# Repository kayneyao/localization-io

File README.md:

# localization-io
An io board for the LSM6DSL 6 axis accel-gyro combo, LIS2MDL 3 axis mag, and ATGMH336H gps module for localization of systems using an RP2040 as the MCU

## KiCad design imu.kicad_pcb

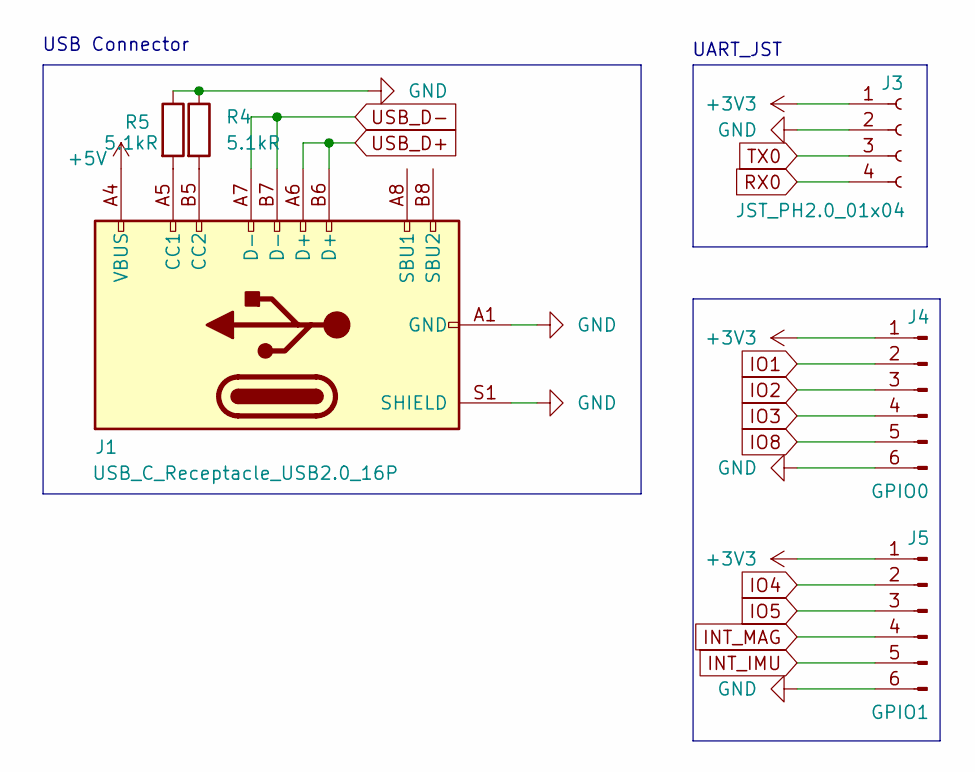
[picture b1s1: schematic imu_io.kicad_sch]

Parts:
J1: USB_C_Receptacle_USB2.0_16P; USB_C_Receptacle_GCT_USB4105-xx-A_16P_TopMnt_Horizontal
J3: JST_PH2.0_01x04; JST_PH_S4B-PH-K_1x04_P2.00mm_Horizontal
J4: GPIO0; PinHeader_1x06_P2.54mm_Vertical
J5: GPIO1; PinHeader_1x06_P2.54mm_Vertical
R4, R5: 5.1kR; R_0805_2012Metric_Pad1.20x1.40mm_HandSolder

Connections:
+3V3: J3.1, J4.1, J5.1; also elsewhere on the board
+5V: J1.A4 (VBUS), J1.A9 (VBUS), J1.B4 (VBUS), J1.B9 (VBUS); also elsewhere on the board
GND: J1.A1 (GND), J1.A12 (GND), J1.B1 (GND), J1.B12 (GND), J1.S1 (SHIELD), J3.2, J4.6, J5.6, R4.1, R5.1; also elsewhere on the board
INT_IMU: J5.5; also elsewhere on the board
INT_MAG: J5.4; also elsewhere on the board
IO1: J4.2; also elsewhere on the board
IO2: J4.3; also elsewhere on the board
IO3: J4.4; also elsewhere on the board
IO4: J5.2; also elsewhere on the board
IO5: J5.3; also elsewhere on the board
IO8: J4.5; also elsewhere on the board
unnamed: J1.A5 (CC1), R5.2
unnamed: J1.B5 (CC2), R4.2
RX0: J3.4; also elsewhere on the board
TX0: J3.3; also elsewhere on the board
USB_D+: J1.A6 (D+), J1.B6 (D+); also elsewhere on the board
USB_D-: J1.A7 (D-), J1.B7 (D-); also elsewhere on the board

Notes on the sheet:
USB Connector
UART_JST

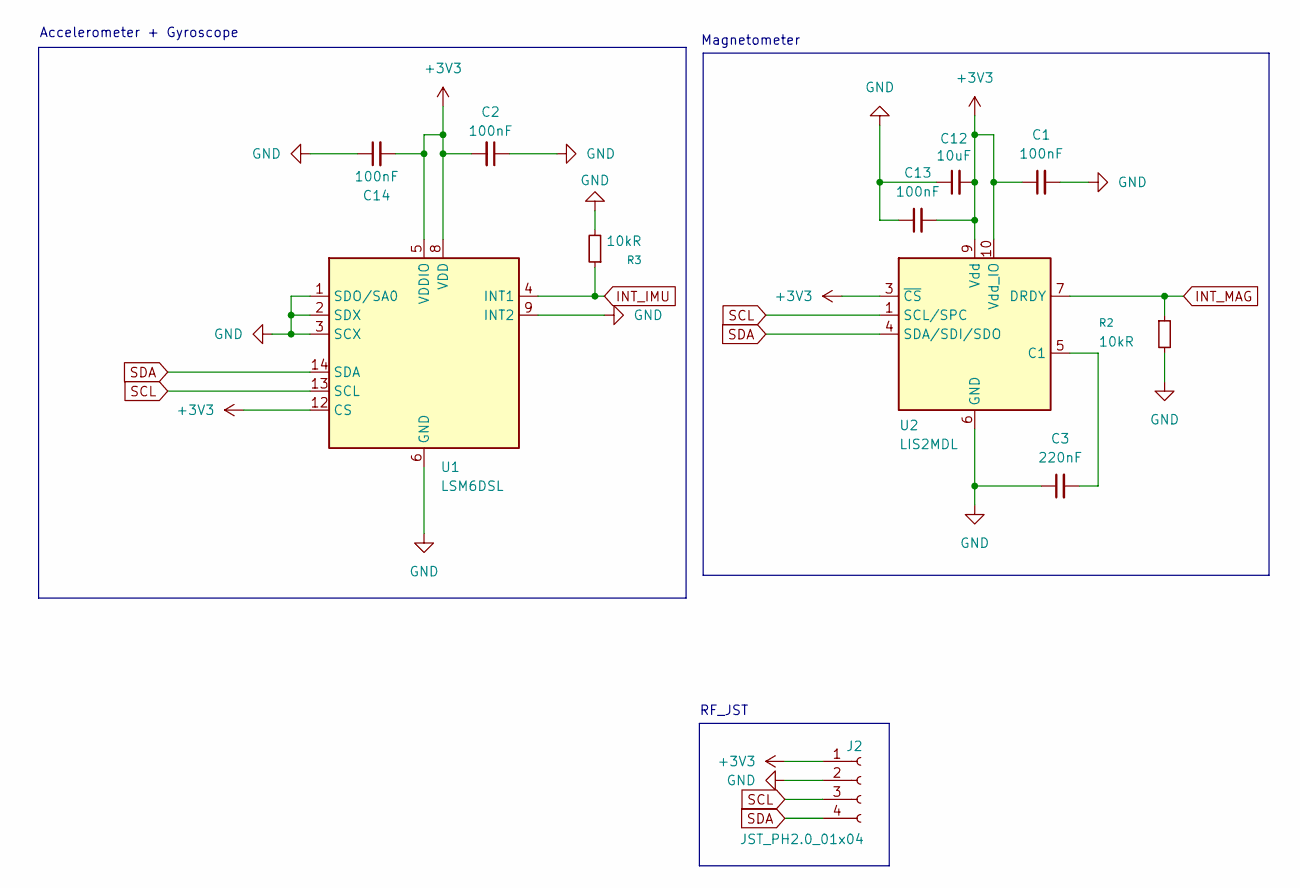
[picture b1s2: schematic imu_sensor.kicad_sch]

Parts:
C1, C2, C13, C14: 100nF; C_0805_2012Metric_Pad1.18x1.45mm_HandSolder
C3: 220nF; C_0805_2012Metric_Pad1.18x1.45mm_HandSolder
C12: 10uF; C_0805_2012Metric_Pad1.18x1.45mm_HandSolder
J2: JST_PH2.0_01x04; JST_PH_S4B-PH-K_1x04_P2.00mm_Horizontal
R2, R3: 10kR; R_0805_2012Metric_Pad1.20x1.40mm_HandSolder
U1: LSM6DSL; LGA-14_3x2.5mm_P0.5mm_LayoutBorder3x4y
U2: LIS2MDL; LGA-12_2x2mm_P0.5mm

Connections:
+3V3: C1.1, C2.2, C12.2, C13.2, C14.2, J2.1, U1.5 (VDDIO), U1.8 (VDD), U1.12 (CS), U2.3 (~CS), U2.9 (Vdd), U2.10 (Vdd_IO); also elsewhere on the board
GND: C1.2, C2.1, C3.1, C12.1, C13.1, C14.1, J2.2, R2.2, R3.2, U1.1 (SDO/SA0), U1.2 (SDX), U1.3 (SCX), U1.6 (GND), U1.7 (GND), U1.9 (INT2), U2.6 (GND), U2.8 (GND); also elsewhere on the board
INT_IMU: R3.1, U1.4 (INT1); also elsewhere on the board
INT_MAG: R2.1, U2.7 (DRDY); also elsewhere on the board
unnamed: C3.2, U2.5 (C1)
SCL: J2.3, U1.13 (SCL), U2.1 (SCL/SPC); also elsewhere on the board
SDA: J2.4, U1.14 (SDA), U2.4 (SDA/SDI/SDO); also elsewhere on the board

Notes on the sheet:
Accelerometer + Gyroscope
RF_JST
Magnetometer

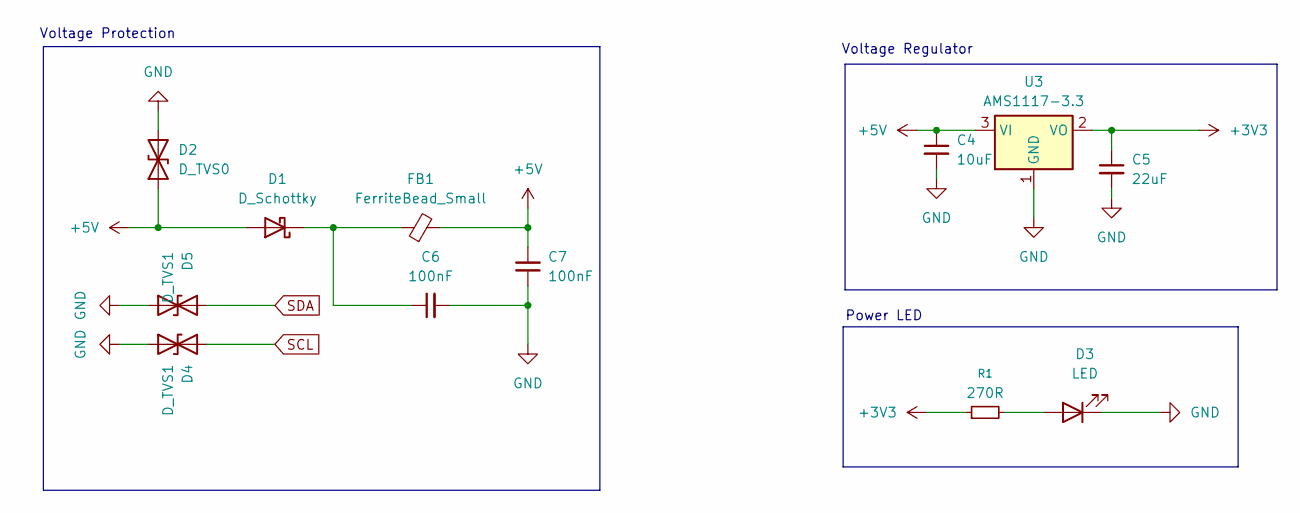
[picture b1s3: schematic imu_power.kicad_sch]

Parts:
C4: 10uF; C_0805_2012Metric_Pad1.18x1.45mm_HandSolder
C5: 22uF; C_0805_2012Metric_Pad1.18x1.45mm_HandSolder
C6, C7: 100nF; C_0805_2012Metric_Pad1.18x1.45mm_HandSolder
D1: D_Schottky; D_SOD-123F
D2: D_TVS0; D_SMB
D3: LED; LED_0805_2012Metric_Pad1.15x1.40mm_HandSolder
D4, D5: D_TVS1; D_SOD-323_HandSoldering
FB1: FerriteBead_Small; L_0805_2012Metric_Pad1.05x1.20mm_HandSolder
R1: 270R; R_0805_2012Metric_Pad1.20x1.40mm_HandSolder
U3: AMS1117-3.3; SOT-223-3_TabPin2

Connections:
+3V3: C5.1, R1.1, U3.2 (VO); also elsewhere on the board
+5V: C4.1, C7.2, D1.2 (A), D2.1 (A1), FB1.2, U3.3 (VI); also elsewhere on the board
GND: C4.2, C5.2, C6.2, C7.1, D2.2 (A2), D3.1 (K), D4.1 (A1), D5.1 (A1), U3.1 (GND); also elsewhere on the board
unnamed: C6.1, D1.1 (K), FB1.1
unnamed: D3.2 (A), R1.2
SCL: D4.2 (A2); also elsewhere on the board
SDA: D5.2 (A2); also elsewhere on the board

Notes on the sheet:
Voltage Protection
Power LED
Voltage Regulator

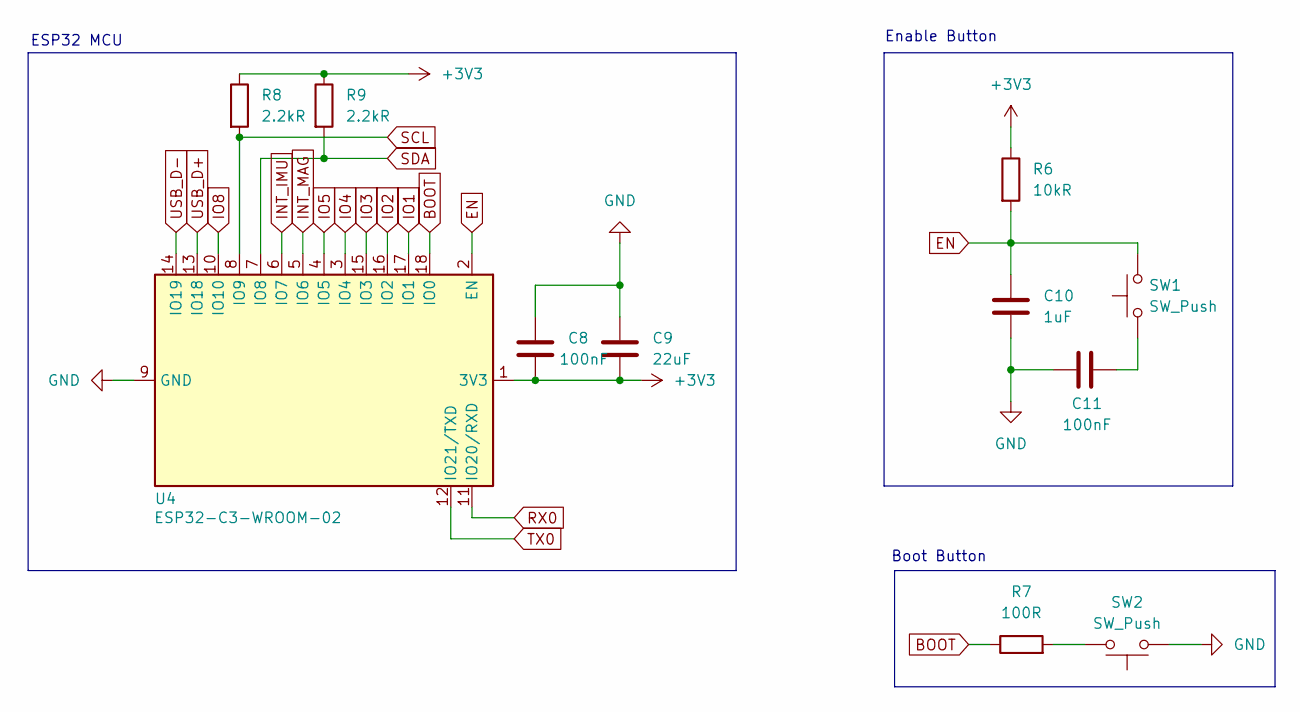
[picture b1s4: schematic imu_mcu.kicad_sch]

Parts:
C8, C11: 100nF; C_0805_2012Metric_Pad1.18x1.45mm_HandSolder
C9: 22uF; C_0805_2012Metric_Pad1.18x1.45mm_HandSolder
C10: 1uF; C_0805_2012Metric_Pad1.18x1.45mm_HandSolder
R6: 10kR; R_0805_2012Metric_Pad1.20x1.40mm_HandSolder
R7: 100R; R_0805_2012Metric_Pad1.20x1.40mm_HandSolder
R8, R9: 2.2kR; R_0805_2012Metric_Pad1.20x1.40mm_HandSolder
SW1, SW2: SW_Push; SW_Tactile_SPST_NO_Straight_CK_PTS636Sx25SMTRLFS
U4: ESP32-C3-WROOM-02

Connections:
+3V3: C8.2, C9.2, R6.1, R8.1, R9.1, U4.1 (3V3); also elsewhere on the board
BOOT: R7.1, U4.18 (IO0)
EN: C10.1, R6.2, SW1.2, U4.2 (EN)
GND: C8.1, C9.1, C10.2, C11.1, SW2.1, U4.9 (GND), U4.19 (GND); also elsewhere on the board
INT_IMU: U4.6 (IO7); also elsewhere on the board
INT_MAG: U4.5 (IO6); also elsewhere on the board
IO1: U4.17 (IO1); also elsewhere on the board
IO2: U4.16 (IO2); also elsewhere on the board
IO3: U4.15 (IO3); also elsewhere on the board
IO4: U4.3 (IO4); also elsewhere on the board
IO5: U4.4 (IO5); also elsewhere on the board
IO8: U4.10 (IO10); also elsewhere on the board
unnamed: C11.2, SW1.1
unnamed: R7.2, SW2.2
RX0: U4.11 (IO20/RXD); also elsewhere on the board
SCL: R8.2, U4.8 (IO9); also elsewhere on the board
SDA: R9.2, U4.7 (IO8); also elsewhere on the board
TX0: U4.12 (IO21/TXD); also elsewhere on the board
USB_D+: U4.13 (IO18); also elsewhere on the board
USB_D-: U4.14 (IO19); also elsewhere on the board

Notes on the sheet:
Boot Button
ESP32 MCU
Enable Button

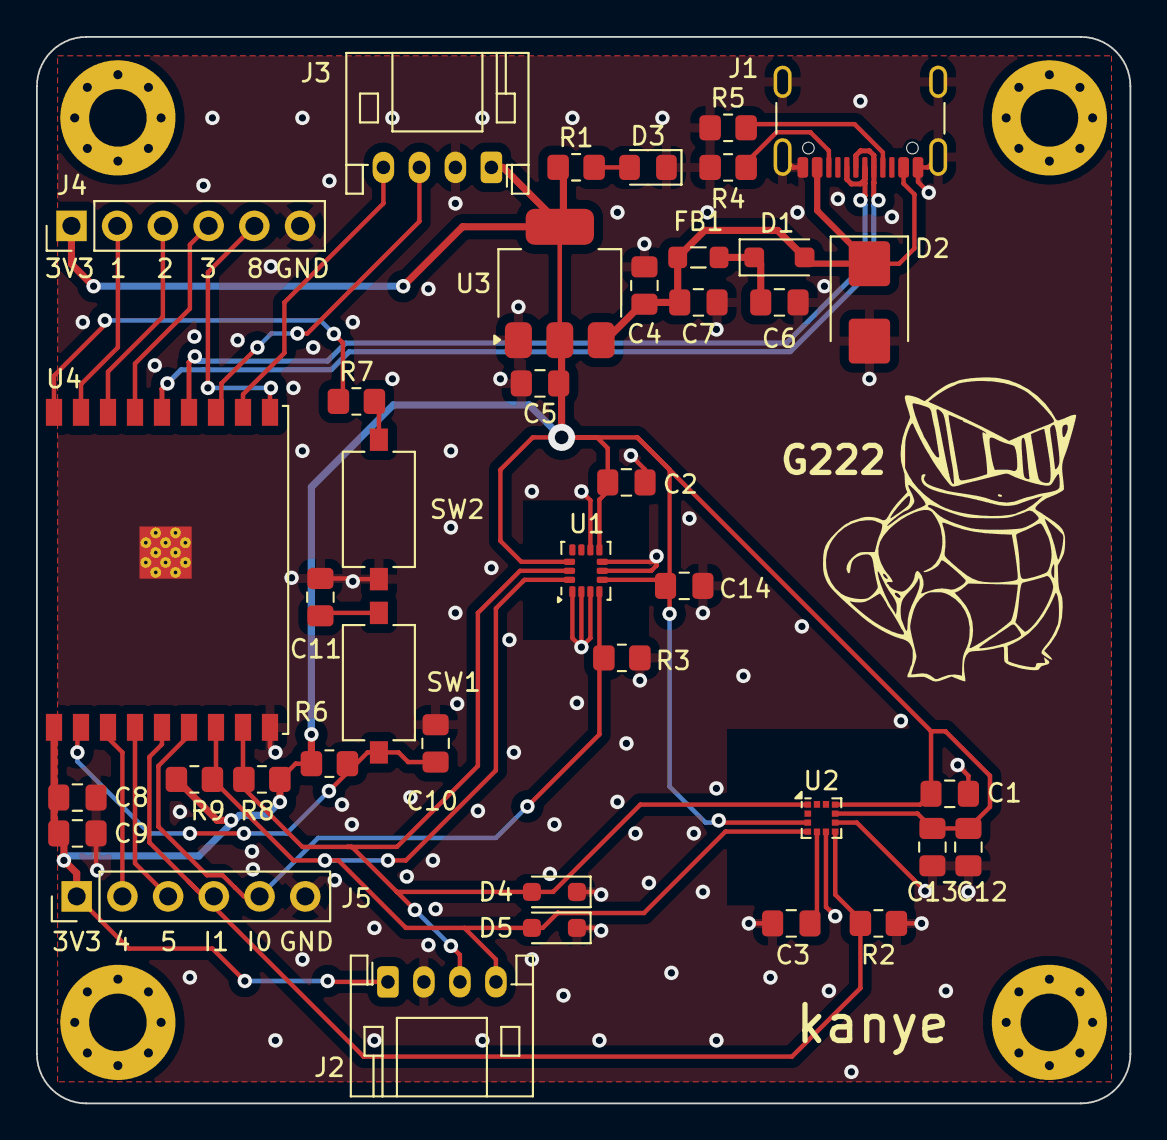
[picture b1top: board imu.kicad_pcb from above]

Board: 4 copper layers, 60.8 x 59.2 mm, 41 parts (0 on the bottom side), 26 nets.

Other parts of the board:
G222: LOGO; Sunglasses_Squirtle

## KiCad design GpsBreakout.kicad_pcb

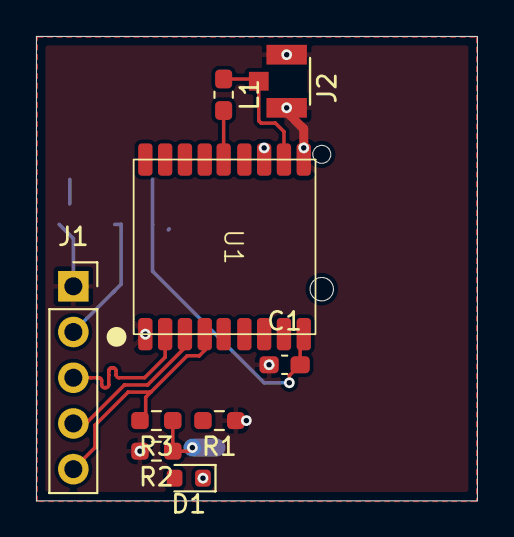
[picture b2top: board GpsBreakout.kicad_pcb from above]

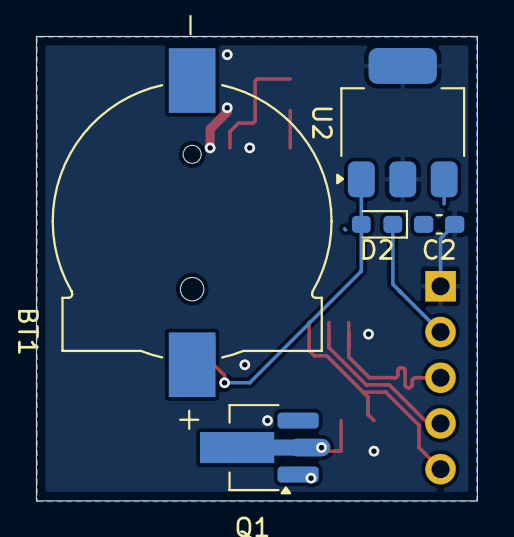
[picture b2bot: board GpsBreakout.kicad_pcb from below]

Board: 4 copper layers, 24.5 x 25.8 mm, 14 parts (5 on the bottom side), 11 nets.

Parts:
BT1: Battery_Cell; BAT_1056TR
C1, C2: 10uF; C_0603_1608Metric_Pad1.08x0.95mm_HandSolder
D1: LED; LED_0603_1608Metric
D2: D; D_0603_1608Metric_Pad1.05x0.95mm_HandSolder
J1: Conn_01x05_Socket; PinSocket_1x05_P2.54mm_Vertical
J2: U.FL Connector; HRS_U.FL-R-SMT_01_
L1: 47nH; L_0603_1608Metric_Pad1.05x0.95mm_HandSolder
Q1: NPN; SOT-89-3_Handsoldering
R1, R2: 100R; R_0603_1608Metric_Pad0.98x0.95mm_HandSolder
R3: 1kR; R_0603_1608Metric_Pad0.98x0.95mm_HandSolder
U1: ATGM336H
U2: AMS1117-3.3; SOT-223-3_TabPin2

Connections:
+3.3V: C1.2, D2.2 (A), U1.9 (VCC), U2.2 (VO)
+5V: C2.2, D1.2 (A), D2.1 (K), J1.2, U2.3 (VI)
GND: C1.1, C2.1, J1.1, J2.1 (GND), J2.2 (GND), R1.1, R2.2, U1.1 (GND), U1.10 (GND), U1.12 (GND), U2.1 (GND)
unnamed: D1.1 (K), Q1.1 (C)
unnamed: J2.3 (SIG), L1.1, U1.11 (RF_IN)
unnamed: Q1.2 (B), R2.1, R3.1
unnamed: Q1.3 (E), R1.2
unnamed: L1.2, U1.14 (VCC_RF)
PPS: J1.5, R3.2, U1.4 (1PPS)
RXD: J1.4, U1.3 (RXD0)
TXD: J1.3, U1.2 (TXD0)

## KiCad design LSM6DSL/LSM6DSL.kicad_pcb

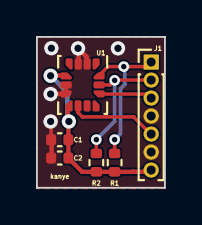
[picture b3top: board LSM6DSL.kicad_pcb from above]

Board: 2 copper layers, 7.1 x 8.4 mm, 6 parts (0 on the bottom side), 6 nets.

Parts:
C1, C2: 100nF; C_0402_1005Metric
J1: Conn_01x07_Male; PinHeader_1x07_P1.00mm_Vertical
R1, R2: 10kR; R_0402_1005Metric
U1: LSM6DSL

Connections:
CS: J1.3 (CS), U1.12 (CS)
GND: C1.2, C2.1, J1.4 (INT1), J1.6 (GND), U1.2 (SDx), U1.3 (SCx), U1.6 (GND), U1.7 (GND)
INT2: J1.5 (INT2), U1.9 (INT2)
SCL: J1.2 (SCL), R2.2, U1.13 (SCL)
SDA: J1.1 (SDA), R1.2, U1.14 (SDA)
VDD: C1.1, C2.2, J1.7 (VCC), R1.1, R2.1, U1.5 (VDDIO), U1.8 (VDD)

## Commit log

2025-05-29 Initial LSM6DSL Files
2025-05-29 Add GPS Breakout Board Files
2025-06-09 Add Sensor Packages to Schematic
2025-06-09 Power and IO Schematics for ICs
2025-06-09 Create Schematic for IMU-Breakout Board
2025-06-10 Add Footprint Names
2025-06-10 PCB Design Finished
2025-06-11 Add Fabrication Outputs
2025-07-02 Add ESP32 and USB-C Recep to Schematic
2025-07-03 Add EN and BOOT Push Buttons
2025-07-03 Add Hierarchal Schematic + JST Connectors + GPIO
2025-07-06 Route Traces for ESP32 and related IO
2025-07-08 Add Sensors and Silkscreen Adjustments
2025-07-08 Move Jumper Text
2025-07-08 Touching up Silkscreen
2025-07-08 Connect USB-C Ground
2025-07-08 Add Silkscreen Labels for Pin Headers
2025-07-20 Finall Fullboard V1
